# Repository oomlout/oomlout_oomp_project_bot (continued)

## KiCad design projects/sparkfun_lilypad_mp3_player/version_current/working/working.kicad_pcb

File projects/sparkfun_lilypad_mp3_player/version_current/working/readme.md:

# OOMP Project  
## LilyPad_MP3_Player  by sparkfun  
  
oomp key: oomp_projects_flat_sparkfun_lilypad_mp3_player  
(snippet of original readme)  
  
SparkFun LilyPad MP3  
========================================  

[*SparkFun LilyPad MP3 (DEV-11013)*](https://www.sparkfun.com/products/11013)  
  
The LilyPad MP3 Player is an amazing little board that contains everything you need to play almost any audio file you wish. You can use it to create MP3-playing hoodies, talking teddy bears, or anything else your imagination can come up with!  
  
--- Installation:  
  
You should install the latest version of the Arduino IDE, available at http://www.arduino.cc.  
  
This software requires several nonstandard libraries:  
	SdFat (by William Greiman)  
	SFEMP3Shield (by Bill Porter)  
	pinChangeInt (by Lex Talionis)  
	  
	The current version of these libraries as of this date are included in this archive.  
  
**TL;DR:** The one-step procedure is to drag the contents of the Arduino folder to your personal Arduino sketch folder. This will create a "libraries" folder (containing support libraries), and a "LilyPad MP3 Player" folder (containing example sketches).  
  
To install the libraries manually, copy the "libraries" folder to your personal Arduino sketch directory. (If there is already a "libraries" folder there, go ahead and add the included libraries to it.) You'll need to restart the Arduino IDE to get it to recognize the new libraries.  
  
To install the example sketches, copy the "LilyPad MP3 Player" folder to your personal Arduino   
  full source readme at [readme_src.md](readme_src.md)  
  
source repo at: [https://github.com/sparkfun/LilyPad_MP3_Player](https://github.com/sparkfun/LilyPad_MP3_Player)  
## Board  

## Schematic  

[schematic pdf](working_schematic.pdf)  
## Images

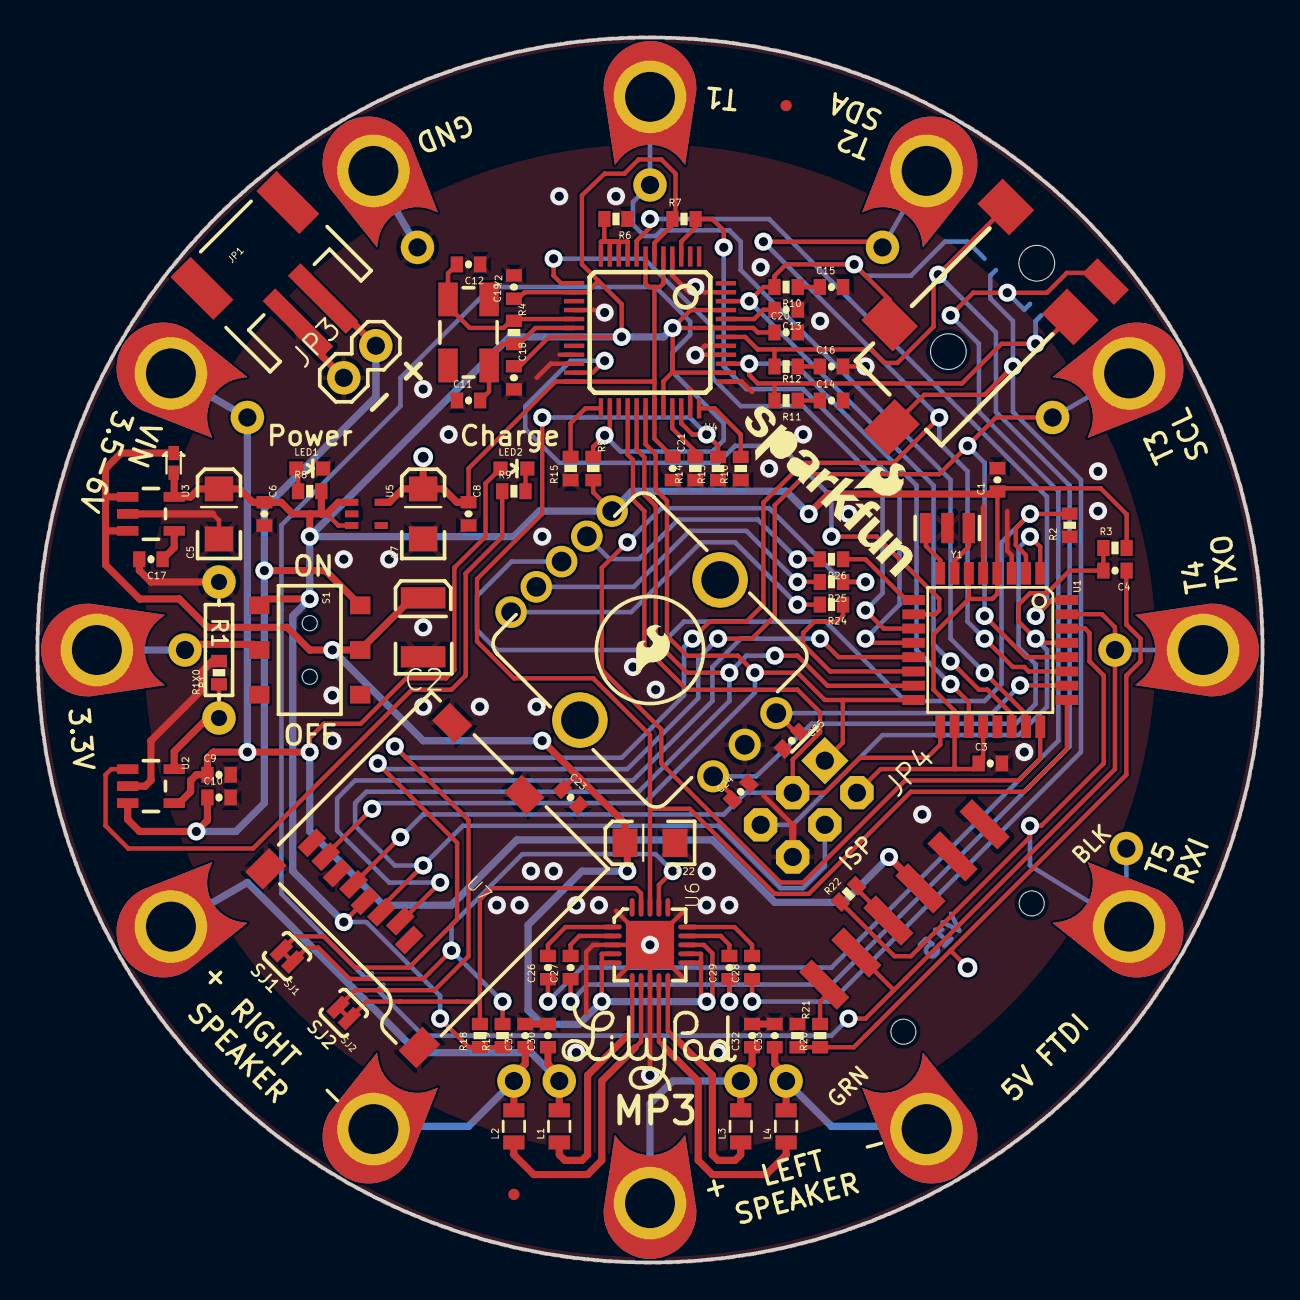
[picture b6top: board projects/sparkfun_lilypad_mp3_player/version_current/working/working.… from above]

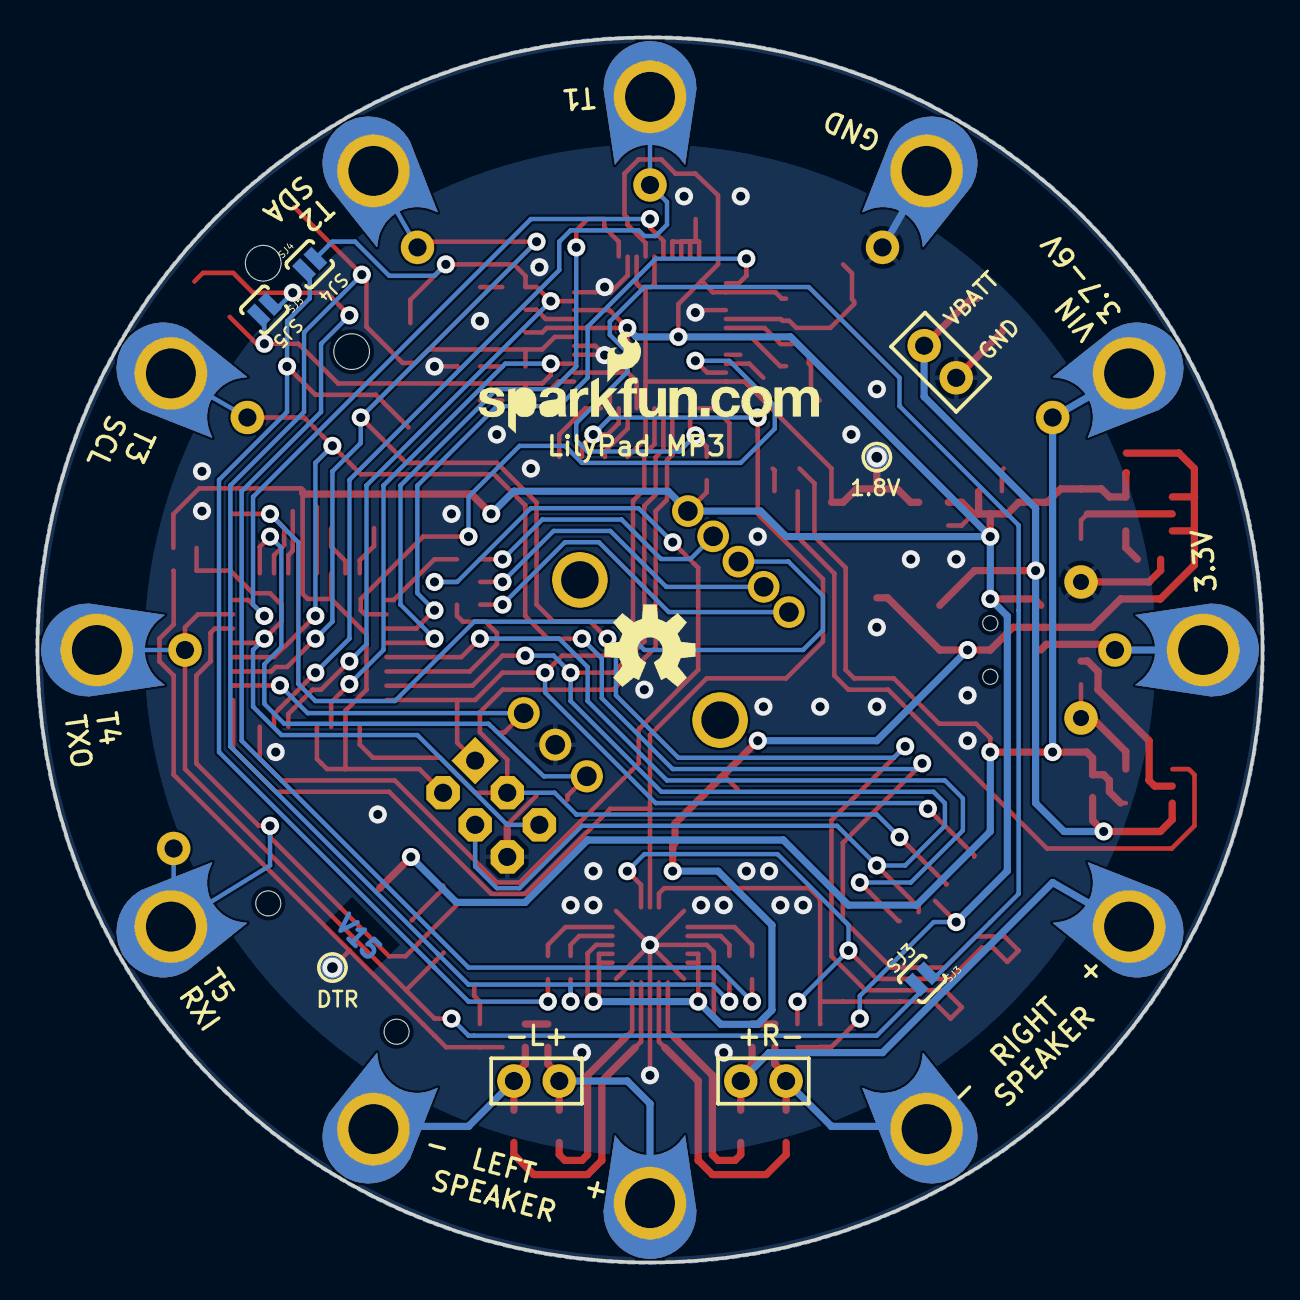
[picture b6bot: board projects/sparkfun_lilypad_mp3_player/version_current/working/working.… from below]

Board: 2 copper layers, 68.6 x 68.6 mm, 121 parts (7 on the bottom side), 69 nets.

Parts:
C1, C4, C6, C8, C18, C19, C20, C21, C23, C24, C25: 0.1uF; 0402-CAP
C2: 47uF; EIA3528
C3, C13, C26, C27, C28, C29: 1uF; 0402-CAP
C5, C7, C22: 10uF; EIA3216
C9, C10: 4.7uF; 0402-CAP
C11, C12: 22pF; 0402-CAP
C14, C15: 10nF; 0402-CAP
C16: 47nF; 0402-CAP
C17: 470pF; 0402-CAP
C30, C31, C32, C33: 1nF; 0402-CAP
D1: SOD-523
JP1: LiPo; JST-2-SMD
JP2: FTDI; 1X06-SMD
JP3: POWER; 1X02
JP4: PROG; 2X3-NS
JP5: HEADPHONE; AUDIO-JACK-3.5MM-SMD
JP6: LOGO-SFENW2; SFE-NEW-WEB
JP7, JP8: FIDUCIALUFIDUCIAL; MICRO-FIDUCIAL
L1, L2, L3, L4: 0805
LED1: RED; LED-0603
LED2: YELLOW; LED-0603
LOGO1, LOGO3: LOGO-SFESK; SFE-LOGO-FLAME
LOGO2: LOGO-SFENEW; SFE-NEW-WEBLOGO
R1, R21: 2K; 0402-RES
R1X0: DNP; AXIAL-0.3
R2, R20: 1K; 0402-RES
R3, R22: 10K; 0402-RES
R4: 1M; 0402-RES
R5, R6, R7, R13, R14, R15, R16: 100k; 0402-RES
R8, R9, R24, R25, R26: 330; 0402-RES
R10, R11: 20; 0402-RES
R12: 10; 0402-RES
R18, R19: 4.7K; 0402-RES
S1: POWER; AYZ0202
S2: EC12PLRGBSDVBF-D; ENCODER_LED_3
SJ1, SJ2, SJ3, SJ4, SJ5: SJ_2S-NO
ST1: TRIG2/SDA; PETAL-LONG-1-2SIDE
ST2: TRIG3/SCL; PETAL-LONG-1-2SIDE
ST3: TRIG4/TXO; PETAL-LONG-1-2SIDE
ST4: TRIG5/RXI; PETAL-LONG-1-2SIDE
ST5: SPKL-; PETAL-LONG-1-2SIDE
ST6: SPKL+; PETAL-LONG-1-2SIDE
ST7: SPKR-; PETAL-LONG-1-2SIDE
ST8: SPKR+; PETAL-LONG-1-2SIDE
ST9: 3.3V; PETAL-LONG-1-2SIDE
ST10: VIN; PETAL-LONG-1-2SIDE
ST11: GND; PETAL-LONG-1-2SIDE
ST12: TRIG1; PETAL-LONG-1-2SIDE
TP1: TRIG1; 1X01NS
TP2: TRIG2/SDA; 1X01NS
TP3: TRIG3/SCL; 1X01NS
TP4: TRIG4/TXO; 1X01NS
TP5: TRIG5/RXI; 1X01NS
TP6: SPKL-; 1X01NS
TP7: SPKL+; 1X01NS
TP8: SPKR-; 1X01NS
TP9: SPKR+; 1X01NS
TP10: 3.3V; 1X01NS
TP11: VIN; 1X01NS
TP12: GND; 1X01NS
TP13: DTR; PAD.03X.05
TP14: 1.8V; PAD.03X.05
U1: ATMEGA328; TQFP32-08
U2: MCP73831; SOT23-5
U3: MIC5219 3.3V; SOT23-5
U4: VS1053; LQFP-48
U5: SP6214 1.8V; SC70
U6: TPA2016D2RTJ; QFN-20-0.5MM
U7: USD-SOCKET; MICRO-SD-SOCKET-PP
U$1: LOGO-LPLP; LOGO-LILYPAD
U$4: OSHW-LOGOM; OSHW-LOGO-M
U$12: CREATIVE_COMMONS
Y1: 8MHz; RESONATOR-SMD
Y2: 12.288MHz; CRYSTAL-SMD-5X3

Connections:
1.8V: C7.A, C8.1, C21.1, TP14.P$1, U4.5, U4.7, U4.24, U4.31, U5.5
3.3V: C1.1, C3.1, C5.A, C6.1, C18.1, C19.1, C20.1, D1.A, JP4.2, R3.2, R5.2, R7.1, R8.2, R18.1, R19.1, S1.4, S2.5, U1.4, U1.6, U1.18, U1.20, U3.5, U4.6, U4.14, U4.19, U4.32, U4.38, U4.43, U4.45, U5.1, U5.3, U7.4
3.3V-TAP: S1.5, ST9.1, TP10.1
AMP-L: C28.1, JP5.TSH, SJ4.1
AMP-LX: C26.2, U6.1
AMP-R: C26.1, JP5.RSH, SJ5.1
AMP-RX: C28.2, U6.15
DTR: C4.1, R20.1, R21.2, TP13.P$1
EN-GPIO1: R13.2, U1.25, U4.34, U6.18
FTDI-DTR: JP2.1, R20.2
FTDI-RXI: JP2.3, R22.2
G1: R6.2, U4.9, U4.10, U4.11, U4.12
G2: R15.2, U4.25
GBUF: C27.1, C29.1, JP5.SLEEVE, R12.2, U4.42
GBUFLX: C27.2, U6.2
GBUFRX: C29.2, U6.14
GND: C1.2, C2.C, C3.2, C5.C, C6.2, C7.C, C8.2, C9.2, C10.2, C11.1, C12.1, C13.1, C14.2, C15.2, C16.2, C17.2, C18.2, C19.2, C20.2, C21.2, C22.C, C23.2, C24.2, C25.2, C30.2, C31.2, C32.2, C33.2, JP1.1, JP2.5, JP2.6, JP3.1, JP4.6, LED1.C, R1.2, R1X0.P$2, R2.1, R6.1, R13.1, R14.1, R15.1, R16.1, R21.1, S2.C, ST11.1, TP12.1, U1.3, U1.5, U1.21, U2.2, U3.2, U4.4, U4.16, U4.20, U4.21, U4.22, U4.35, U4.37, U4.40, U4.41, U4.47, U5.2, U6.3, U6.8, U6.PAD, U7.6, U7.CD1, U7.CD2, U7.GND1, U7.GND3, Y1.2
GPIO0: R14.2, U4.33
LEFT: JP5.TIP, R10.2, SJ4.2, U1.22, U4.46
MISO: JP4.1, U1.16, U4.30, U7.7
MOSI: JP4.4, U1.15, U4.29, U7.3
MP3-CS: U1.10, U4.23
MP3-DCS: U1.11, U4.13
MP3-DREQ: U1.32, U4.8
MP3-MIDI-RX: R5.1, SJ3.1, U4.26
MP3-RST: R7.2, U1.12, U4.3
unnamed: U1.7, Y1.1
unnamed: U1.8, Y1.3
unnamed: C13.2, U4.44
unnamed: C16.1, R12.1
unnamed: LED1.A, R8.1
unnamed: C15.1, R10.1
unnamed: LED2.C, R9.2
unnamed: C11.2, R4.2, U4.18, Y2.3
unnamed: C12.2, R4.1, U4.17, Y2.1
unnamed: C14.1, R11.1
unnamed: R24.2, S2.1
unnamed: R25.2, S2.2
unnamed: R26.2, S2.4
unnamed: L1.1, U6.6
unnamed: L2.1, U6.7
unnamed: L3.1, U6.10
unnamed: L4.1, U6.9
unnamed: C17.1, U3.4
unnamed: R16.2, U4.36
PROG: R1.1, R1X0.P$1, U2.5
RIGHT: JP5.RING, R11.2, SJ5.2, U1.19, U4.39
ROT-A: C24.1, S2.A, U1.1
ROT-B: C25.1, S2.B, U1.26
ROT-LEDB: R26.1, U1.9
ROT-LEDG: R25.1, U1.24
ROT-LEDR: R24.1, U1.14
ROT-SW: R2.2, S2.3, U1.2
RST: C4.2, JP4.5, R3.1, U1.29
SCK: JP4.3, U1.17, U4.28, U7.5
SD-CS: U1.13, U7.2
SPKL+: C32.1, L3.2, ST6.1, TP7.1
SPKL-: C33.1, L4.2, ST5.1, TP6.1
SPKR+: C30.1, L1.2, ST8.1, TP9.1
SPKR-: C31.1, L2.2, ST7.1, TP8.1
STAT: R9.1, U2.1
TRIG1: ST12.1, TP1.1, U1.23
TRIG2/SDA: R18.2, SJ2.1, SJ2.2, ST1.1, TP2.1, U1.27, U6.19
TRIG3/SCL: R19.2, SJ1.1, SJ1.2, ST2.1, TP3.1, U1.28, U6.17
TRIG4/TXO: JP2.2, SJ3.2, ST3.1, TP4.1, U1.31
TRIG5/RXI: R22.1, ST4.1, TP5.1, U1.30
VBATT: C10.1, JP1.2, JP3.2, S1.1, U2.3
VBATT_SW: C2.A, C22.A, C23.1, D1.C, S1.2, U3.1, U3.3, U6.4, U6.5, U6.11, U6.12, U6.13
VIN: C9.1, JP2.4, LED2.A, ST10.1, TP11.1, U2.4

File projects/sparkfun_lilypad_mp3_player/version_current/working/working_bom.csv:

"Id";"Designator";"Footprint";"Quantity";"Designation";"Supplier and ref";
1;"Y2";"CRYSTAL-SMD-5X3";1;"12.288MHz";;;
2;"ST10";"PETAL-LONG-1-2SIDE";1;"VIN";;;
3;"ST2";"PETAL-LONG-1-2SIDE";1;"TRIG3/SCL";;;
4;"JP3";"1X02";1;"POWER";;;
5;"TP10";"1X01NS";1;"3.3V";;;
6;"C29,C28,C26,C27,C13,C3";"0402-CAP";6;"1uF";;;
7;"R8,R9,R26,R24,R25";"0402-RES";5;"330";;;
8;"ST1";"PETAL-LONG-1-2SIDE";1;"TRIG2/SDA";;;
9;"R14,R16,R5,R7,R15,R6,R13";"0402-RES";7;"100k";;;
10;"C20,C8,C19,C4,C21,C24,C6,C1,C23,C18,C25";"0402-CAP";11;"0.1uF";;;
11;"TP8";"1X01NS";1;"SPKR-";;;
12;"D1";"SOD-523";1;"";;;
13;"U1";"TQFP32-08";1;"ATMEGA328";;;
14;"R3,R22";"0402-RES";2;"10K";;;
15;"U$12";"CREATIVE_COMMONS";1;"CREATIVE_COMMONS";;;
16;"S2";"ENCODER_LED_3";1;"EC12PLRGBSDVBF-D";;;
17;"R11,R10";"0402-RES";2;"20";;;
18;"C17";"0402-CAP";1;"470pF";;;
19;"C5,C22,C7";"EIA3216";3;"10uF";;;
20;"ST9";"PETAL-LONG-1-2SIDE";1;"3.3V";;;
21;"S1";"AYZ0202";1;"POWER";;;
22;"R21,R1";"0402-RES";2;"2K";;;
23;"U$1";"LOGO-LILYPAD";1;"LOGO-LPLP";;;
24;"C16";"0402-CAP";1;"47nF";;;
25;"LED1";"LED-0603";1;"RED";;;
26;"R20,R2";"0402-RES";2;"1K";;;
27;"L3,L1,L2,L4";"0805";4;"";;;
28;"LED2";"LED-0603";1;"YELLOW";;;
29;"C10,C9";"0402-CAP";2;"4.7uF";;;
30;"C2";"EIA3528";1;"47uF";;;
31;"Y1";"RESONATOR-SMD";1;"8MHz";;;
32;"U6";"QFN-20-0.5MM";1;"TPA2016D2RTJ";;;
33;"U5";"SC70";1;"SP6214 1.8V";;;
34;"R12";"0402-RES";1;"10";;;
35;"TP11";"1X01NS";1;"VIN";;;
36;"LOGO1,LOGO3";"SFE-LOGO-FLAME";2;"LOGO-SFESK";;;
37;"ST11";"PETAL-LONG-1-2SIDE";1;"GND";;;
38;"ST5";"PETAL-LONG-1-2SIDE";1;"SPKL-";;;
39;"ST7";"PETAL-LONG-1-2SIDE";1;"SPKR-";;;
40;"R18,R19";"0402-RES";2;"4.7K";;;
41;"SJ1,SJ2,SJ5,SJ4,SJ3";"SJ_2S-NO";5;"";;;
42;"ST8";"PETAL-LONG-1-2SIDE";1;"SPKR+";;;
43;"R4";"0402-RES";1;"1M";;;
44;"C30,C33,C31,C32";"0402-CAP";4;"1nF";;;
45;"TP4";"1X01NS";1;"TRIG4/TXO";;;
46;"U3";"SOT23-5";1;"MIC5219 3.3V";;;
47;"JP2";"1X06-SMD";1;"FTDI";;;
48;"TP6";"1X01NS";1;"SPKL-";;;
49;"TP3";"1X01NS";1;"TRIG3/SCL";;;
50;"C15,C14";"0402-CAP";2;"10nF";;;
51;"TP9";"1X01NS";1;"SPKR+";;;
52;"JP7,JP8";"MICRO-FIDUCIAL";2;"FIDUCIALUFIDUCIAL";;;
53;"TP7";"1X01NS";1;"SPKL+";;;
54;"JP1";"JST-2-SMD";1;"LiPo";;;
55;"R1X0";"AXIAL-0.3";1;"DNP";;;
56;"ST4";"PETAL-LONG-1-2SIDE";1;"TRIG5/RXI";;;
57;"TP1";"1X01NS";1;"TRIG1";;;
58;"TP12";"1X01NS";1;"GND";;;
59;"C11,C12";"0402-CAP";2;"22pF";;;
60;"ST12";"PETAL-LONG-1-2SIDE";1;"TRIG1";;;
61;"U7";"MICRO-SD-SOCKET-PP";1;"USD-SOCKET";;;
62;"U2";"SOT23-5";1;"MCP73831";;;
63;"JP6";"SFE-NEW-WEB";1;"LOGO-SFENW2";;;
64;"U4";"LQFP-48";1;"VS1053";;;
65;"JP4";"2X3-NS";1;"PROG";;;
66;"TP5";"1X01NS";1;"TRIG5/RXI";;;
67;"TP2";"1X01NS";1;"TRIG2/SDA";;;
68;"ST6";"PETAL-LONG-1-2SIDE";1;"SPKL+";;;
69;"ST3";"PETAL-LONG-1-2SIDE";1;"TRIG4/TXO";;;
70;"JP5";"AUDIO-JACK-3.5MM-SMD";1;"HEADPHONE";;;
71;"LOGO2";"SFE-NEW-WEBLOGO";1;"LOGO-SFENEW";;;
72;"U$4";"OSHW-LOGO-M";1;"OSHW-LOGOM";;;
73;"TP13";"PAD.03X.05";1;"DTR";;;
74;"TP14";"PAD.03X.05";1;"1.8V";;;

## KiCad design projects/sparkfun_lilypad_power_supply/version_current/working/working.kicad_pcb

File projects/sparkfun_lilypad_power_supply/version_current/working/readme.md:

# LilyPad_Power_Supply by sparkfun  
This is a harvested standardized copy of a project from github.  
The original project can be found at:  
https://github.com/sparkfun/LilyPad_Power_Supply  
Please consult that link for additional, details, files, and license information.  
Note: It was auto harvested and if the original repo had more than one board file or anything out of the ordinary the files here are likely not representative.

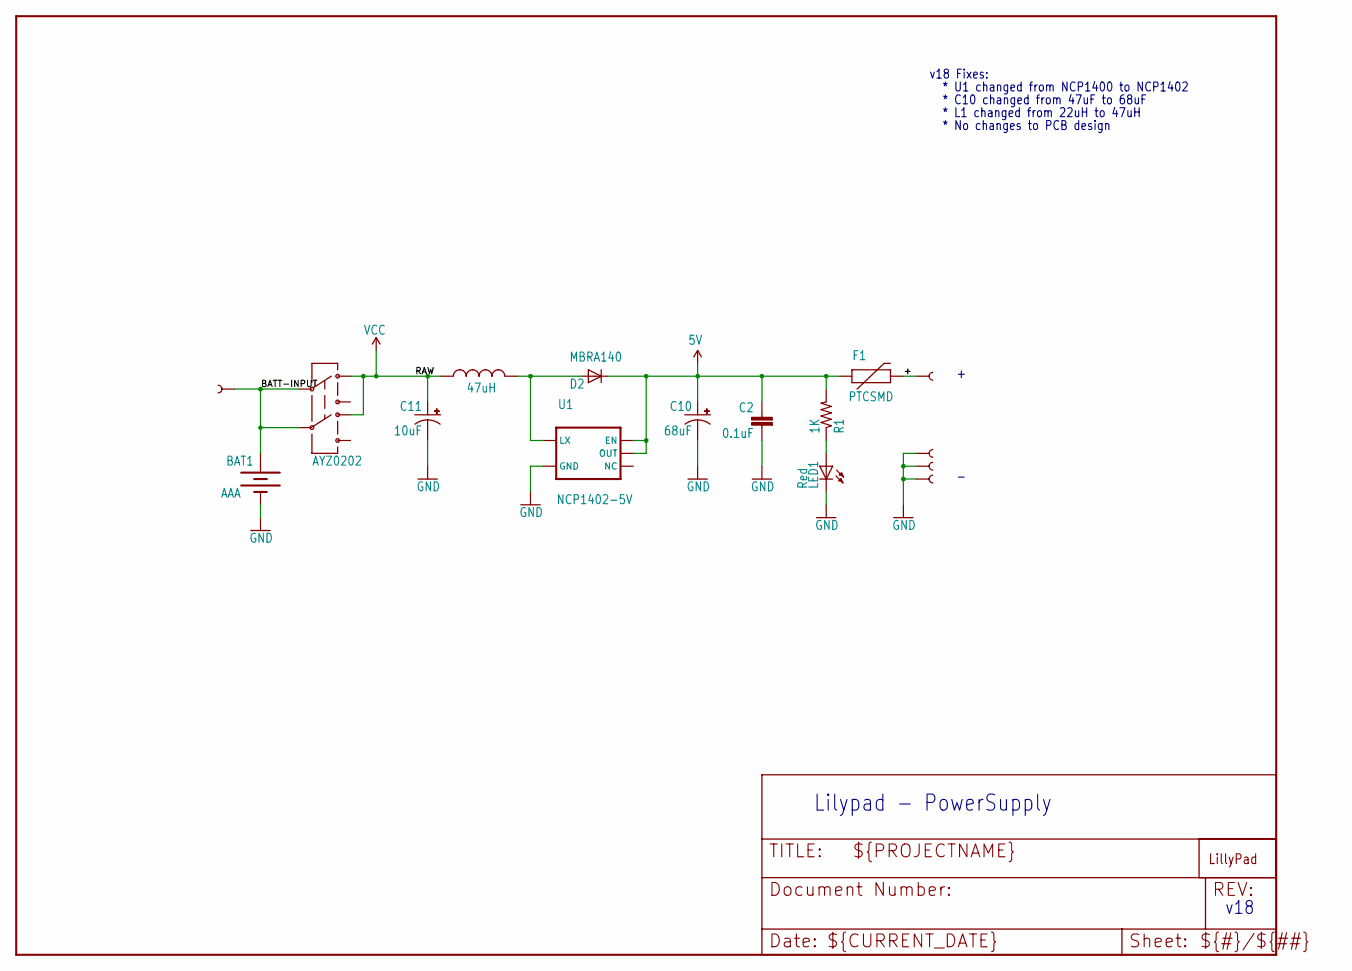
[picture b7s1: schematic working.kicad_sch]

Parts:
BAT1: AAA; BATTERY-AAA
C2: 0.1uF; 0603-CAP
C10: 68uF; EIA3528-21
C11: 10uF; CPOL_1206
D2: MBRA140; SMA-DIODE
F1: PTCSMD; PTC-1206
L1: 47uH; CR54
LED1: Red; LED-1206
R1: 1K; 0603-RES
S1: AYZ0202
TP1: TEST-POINT3X5; PAD.03X.05
U1: NCP1402-5V; SOT23-5
U$1, U$2, U$4, U$5: SEWTAP10; PETAL-LONG-2-2SIDE
U$7: LOGO-LPLP; LOGO-LILYPAD

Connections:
5V: C2.1, C10.A (+), D2.C, F1.1, R1.2, U1.1 (EN), U1.2 (OUT)
+: F1.2, U$1.1
BATT-INPUT: BAT1.PWR@1 (+), S1.2, S1.5, TP1.P$1
GND: BAT1.GND@1 (-), C2.2, C10.C (-), C11.C (-), LED1.C, U1.4 (GND), U$2.1, U$4.1, U$5.1
unnamed: LED1.A, R1.1
unnamed: D2.A, L1.P$1 (1), U1.5 (LX)
RAW: C11.A (+), L1.P$2 (2), S1.3 (1), S1.6 (4)

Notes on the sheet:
* L1 changed from 22uH to 47uH
* U1 changed from NCP1400 to NCP1402
v18
* C10 changed from 47uF to 68uF
* No changes to PCB design
v18 Fixes:
Lilypad - PowerSupply

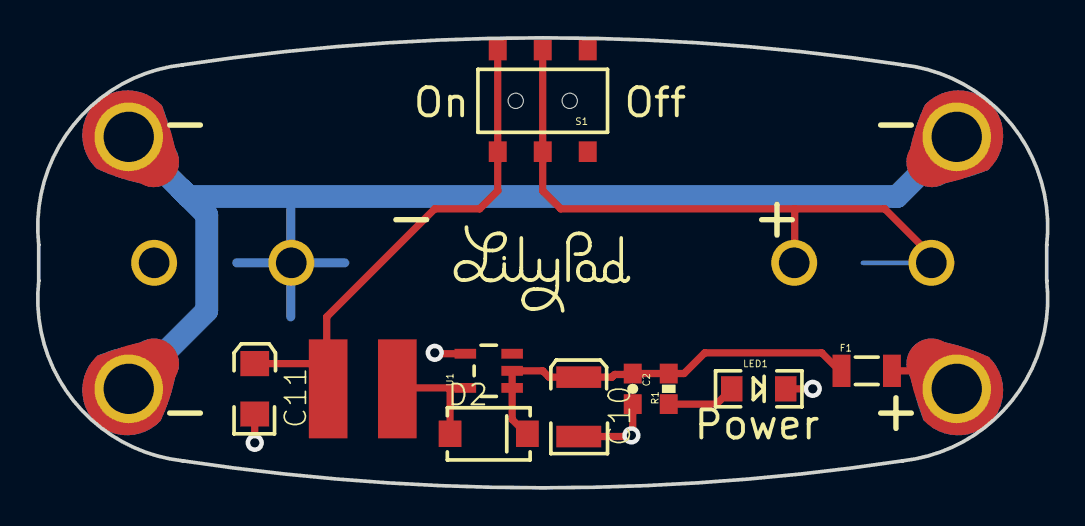
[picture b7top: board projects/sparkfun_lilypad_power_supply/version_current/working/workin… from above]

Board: 2 copper layers, 56.1 x 25.0 mm, 17 parts (1 on the bottom side), 7 nets.
